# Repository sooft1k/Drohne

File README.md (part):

# Drohne – Flugsteuerung STM32F405

Eigene Flugsteuerung für einen Quadrocopter mit STM32F405RGT6 (STM32-HAL).

Dieser Branch gilt für die neue Platine. Die Firmware ist bisher nur kompiliert
und noch nicht auf der Platine getestet.

| Teil | Anschluss |
|---|---|
| Gyro/Accel | ICM-42688-P an SPI1 (PA4 CS, PA5 SCK, PA6 MISO, PA7 MOSI), 10,5 MHz |
| Barometer | BMP388 an I2C1 (PB6 SCL, PB7 SDA), Adresse 0x76, 400 kHz |
| Kompass | QMC5883L an I2C1, Adresse 0x0D |
| Abstand (ToF) | 5× VL53L1X an I2C3 (PA8 SCL, PC9 SDA), Adressen 0x30–0x34, 400 kHz; je eigenes XSHUT und Interrupt |
| GPS | ATGM336H-6N-74 an USART3 (PB10 TX, PB11 RX), 115200 Baud, NMEA |
| Motoren | TIM3, Oneshot125: M1 = PB0, M2 = PB1, M3 = PC6, M4 = PC7; 143,5–229 µs (BLHeli_S ab Werk), Stopp 125 µs |
| Funk | ELRS-Empfänger, CRSF 420000 Baud an USART1 (PA9 TX, PA10 RX) |
| Kanäle | 1 Roll, 2 Pitch, 3 Gas, 4 Yaw, 7 Modus Angle/Rate, **8 Arm-Schalter (AUX4)** |
| Terminal | USART2 (PA2 TX, PA3 RX), 115200 Baud, über einen USB-Seriell-Adapter |
| Akkuspannung | PC0 (ADC1 Kanal 10), Teiler 11:1 |
| Strom | PC1 (ADC2 Kanal 11), Stromausgang „C“ des ESC – höchstens 3,3 V! |
| Status-LED | PC13, aktiv-low (Low = an) |

Regeltakt 1 kHz über TIM2. Flugmodi Angle (selbstaufrichtend) und Rate (Acro).

> **Arm-Schalter auf Kanal 8 (AUX4)**, Modus-Schalter auf Kanal 7. Mit Funk
> zeigt `rc` beide Kanäle; Kanal 8 muss beim Umlegen zwischen etwa 1000 und
> 2000 wechseln. Vor dem ersten Flug Schritt 20 des Kipptests prüfen.
> Kanal 5 (AUX1) wäre bei ELRS etwas schneller, lässt sich an der
> RadioMaster T8L aber keinem Schalter zuordnen – siehe „Arm-Schalter und
> ELRS“ unter „Failsafe“. Kanal in `RC_CH_ARM` (`Sensors/rc.h`).

## Verdrahtung (eigene Platine)

Dieser Abschnitt beschreibt den Zielzustand. Im Schaltplan fehlen Stand
06.11.2026 noch ESC, ELRS, Terminal, Status-LED und die Messung an PC0 und PC1.
Die Namen Ro, Ru, Cb, Rs und Cs gelten nur in dieser README, im Schaltplan haben
die Bauteile andere Nummern.

Alle Massen (GND) sind miteinander verbunden: Akku-Minus über den ESC, die
Flugsteuerung, Empfänger und der USB-Seriell-Adapter. **Beim Löten
und Anstecken immer zuerst GND verbinden**, dann die Signale.

### Übersicht

| Von | An STM32 | Hinweis |
|---|---|---|
| ESC M1 / M2 / M3 / M4 | PB0 / PB1 / PC6 / PC7 | je 10 kΩ nach GND empfohlen (siehe unten) |
| ESC GND | GND | gemeinsame Masse, Pflicht |
| ESC Strom „C“/„CUR“ | PC1 über 4,7 kΩ, 100 nF nach GND | höchstens 3,3 V am Pin |
| Akku+ (z. B. ESC-Pin „V“/„VBAT“) | PC0 über Teiler 10 kΩ / 1 kΩ, 100 nF | Teiler 11:1 |
| ELRS TX | PA10 (USART1 RX) | |
| ELRS RX | PA9 (USART1 TX) | für die Akku-Telemetrie |
| ELRS 5V / GND | 5 V / GND | |
| ICM-42688-P CS / SCK / MISO / MOSI | PA4 / PA5 / PA6 / PA7 (SPI1) | auf der Platine |
| BMP388 und QMC5883L SCL / SDA | PB6 / PB7 (I2C1) | auf der Platine |
| VL53L1X SCL / SDA | PA8 / PC9 (I2C3) | auf der Platine, Pullups 4,7 kΩ (R16, R17) |
| VL53L1X XSHUT 1–5 | PC8, PB12, PB13, PB14, PB15 | je 10 kΩ nach 3,3 V |
| VL53L1X GPIO1 (INT) 1–5 | PC2, PB4, PB5, PB8, PB9 | je 10 kΩ nach 3,3 V |
| GPS TXD / RXD | PB11 / PB10 (USART3) | auf der Platine |
| USB-Seriell RX / TX | PA2 / PA3 (USART2) | 3,3-V-Pegel, 115200 Baud |
| Status-LED | PC13 über LED und 1 kΩ an +3,3 V | aktiv-low |

### 1. Akkuspannung an PC0

```
 Akku+ (VBAT, bis 25,2 V)
        │
       ┌┴┐
       │ │ Ro  10 kΩ, 1 %, 0,25 W
       └┬┘
        │
        ├──────────┬──────────── PC0  (ADC1, Kanal 10)
        │          │
       ┌┴┐       ──┴──
       │ │ Ru    ─────  Cb  100 nF, Keramik X7R
       └┬┘ 1 kΩ    │
        │   1 %    │
 GND ───┴──────────┴──────────── GND STM32 (= Akku-Minus über den ESC)
```

- **Ro = 10 kΩ, Ru = 1 kΩ**, Metallschicht, 1 %. Teilerfaktor 11:
  25,2 V (6S voll) → 2,29 V an PC0.
- Leistung bei 25,2 V: 25,2² / 11 kΩ ≈ 58 mW im ganzen Teiler, davon rund 52 mW
  in Ro – 0,25-W-Widerstand reicht.
- **Cb = 100 nF** direkt an PC0 nach GND, glättet Störungen der Motoren.
- Ru und Cb möglichst nah am STM32-Pin löten, die lange Leitung kommt an Ro.
- Andere Widerstände gehen auch, dann aber `BAT_R_OBEN` und `BAT_R_UNTEN` in
  `Sensors/battery.h` anpassen. PC0 darf nie mehr als 3,3 V sehen.
- Nach dem ersten Anstecken mit einem Multimeter die Akkuspannung messen
  und `batcal <volt>` eingeben.

### 2. Stromeingang PC1 schützen

```
 ESC "C" / "CUR"
        │
       ┌┴┐
       │ │ Rs  4,7 kΩ
       └┬┘
        │
        ├──────────────────────── PC1  (ADC2, Kanal 11)
        │
      ──┴──
      ─────  Cs  100 nF, Keramik X7R
        │
 GND ───┴──────────────────────── GND STM32
```

- **Rs = 4,7 kΩ in Reihe, Cs = 100 nF von PC1 nach GND**, beide direkt am Pin.
  Zusammen ein Tiefpass mit etwa 340 Hz: Er glättet die PWM-Welligkeit des
  ESC (24/48 kHz), und Rs begrenzt den Strom, falls der Ausgang doch über
  3,3 V geht.
- PC1 verträgt als Analogeingang **höchstens 3,3 V**. Deshalb vorher messen (siehe Punkt 3). Kann
  der Ausgang über 3,0 V gehen, statt Rs allein einen Teiler einbauen:

```
 ESC "C" ──[ 10 kΩ ]──┬── PC1
                      ├──[ 20 kΩ ]── GND
                      └──|| 100 nF ── GND
```

  Der Teiler macht aus 4,5 V dann 3,0 V. Danach `CURR_MV_PER_A_DEFAULT` in
  `battery.h` mit 2/3 multiplizieren (bzw. einfach mit `curcal`
  kalibrieren).

### 3. Woher das Stromsignal kommt

Der B-Cube-4in1 hat einen Stromsensor (Shunt mit Verstärker) für alle vier
Motoren zusammen. Sein Ausgang liegt am 8-poligen Stecker zur Flugsteuerung,
beschriftet mit **„C“, „CUR“ oder „CURR“**. Die Pin-Reihenfolge ist je nach
Version verschieden. Aus der früheren Platinenplanung war sie
`1 GND · 2 VBAT · 3 M1 · 4 M2 · 5 M3 · 6 M4 · 7 C · 8 frei` – **trotzdem am
Aufdruck neben dem Stecker prüfen**, nicht dem Kabel vertrauen.

Mit dem Multimeter (Akku dran, Propeller ab, Motoren aus):

1. **GND:** Durchgang zum Akku-Minus.
2. **VBAT:** zeigt die Akkuspannung.
3. **C/CUR:** zeigt 0 V bis einige 10 mV. Nach dem Armen (Motoren im
   Leerlauf) steigt der Wert leicht. Bei 12,75 mV/A macht 1 A nur 13 mV
   aus.
4. **Höchstwert:** Die Skalierung ist nicht bekannt (12–40 mV/A üblich). Bei
   40 mV/A wären 3,3 V schon bei 82 A erreicht – das kann ein 5-Zoll-Quad
   bei Vollgas erreichen. Deshalb prüfen, woher der Verstärker seine Versorgung
   bekommt: Ist auf der ESC-Platine nur eine 3,3-V-Schiene in der Nähe,
   kann der Ausgang nicht über 3,3 V gehen. Ist es 5 V, den Teiler aus
   Punkt 2 nehmen.

Der Pin „TLM“ (falls vorhanden) bleibt frei – BLHeli_S sendet keine
Telemetrie.

### 4. Motorsignale

```
 PB0 ──┬──── ESC M1        (ebenso PB1→M2, PC6→M3, PC7→M4)
       │
      ┌┴┐
      │ │ 10 kΩ nach GND (empfohlen)
      └┬┘
 GND ──┴──── ESC GND
```

Nach einem Reset sind die STM32-Pins einige Millisekunden lang offen. Liegt
eine Signalleitung dabei auf High, während der ESC startet, kann BLHeli_S in
seinen Bootloader springen und erst wieder reagieren, wenn das Signal läuft. Ein 10-kΩ-Widerstand nach GND an jeder Leitung hält
sie in dieser Zeit sicher auf Low.

### Bauteilliste

| Bauteil | Wert | Anzahl | Wofür |
|---|---|---|---|
| Widerstand 1 %, 0,25 W | 10 kΩ | 1 | Ro Akkuteiler |
| Widerstand 1 % | 1 kΩ | 1 | Ru Akkuteiler |
| Widerstand | 4,7 kΩ | 1 | Rs Strom |
| Widerstand | 10 kΩ | 4 | Pull-down Motorsignale |
| Keramikkondensator X7R | 100 nF | 2 | Cb an PC0, Cs an PC1 |
| optional Widerstand | 10 kΩ + 20 kΩ | je 1 | Teiler am Strom, falls > 3,0 V |

## ESC und Motorsignal (BLHeli_S)

**Der ESC muss nicht umprogrammiert werden.** Die Firmware gibt genau den
Gasbereich aus, den BLHeli_S ab Werk erwartet: PPM Min/Max Throttle
1148/1832 µs, bei Oneshot125 geteilt durch 8.

| Zustand | Pulsbreite | Konstante (`Sensors/motor.h`) |
|---|---|---|
| Disarmed, Start, Notaus | 125 µs – sicher unter dem Minimum, der ESC steht und armt | `MOTOR_US_STOP` |
| Gearmt, 0 % Ausgang | 143,5 µs = ESC-Minimum, Motor steht gerade noch | `MOTOR_US_MIN` |
| Gearmt, Leerlauf | 147,8 µs = 5 % (`MIXER_IDLE_PERCENT`) | |
| Gearmt, 100 % Ausgang | 229 µs = ESC-Maximum | `MOTOR_US_MAX` |

Der Stopp-Puls von 125 µs liegt weit unter dem Maximum – der ESC geht beim
Einschalten nicht in den Programmiermodus (der startet nur, wenn beim
Einschalten Vollgas anliegt).

**Leerlauf prüfen** (Kipptest Schritt 15): Alle vier Motoren müssen im
Leerlauf sicher und gleichmäßig drehen. Stockt einer oder läuft er
unruhig an, `MIXER_IDLE_PERCENT` in `Sensors/mixer.h` in Schritten von 1 %
erhöhen; drehen sie unnötig schnell, senken (nicht unter 2 %).

**Drehrichtung** ohne Linker: Dreht ein Motor falsch herum, zwei seiner drei
Motordrähte tauschen.

### Optional: ESC umprogrammieren

Wer später einen BLHeli-Linker hat (fertiger USB-Linker, Arduino mit der
4-Way-Interface-Firmware aus BLHeliSuite oder vorübergehend eine
Betaflight-Flugsteuerung mit [esc-configurator.com](https://esc-configurator.com)),
kann den Gasbereich etwas weiter stellen und „Programming by TX“
abschalten. Die eigene Flugsteuerung kann kein BLHeli-Passthrough.

| Einstellung | Wert | dann in `motor.h` |
|---|---|---|
| PPM Min Throttle | 1040 µs | `MOTOR_US_MIN 130.0f` |
| PPM Max Throttle | 2000 µs | `MOTOR_US_MAX 250.0f` |
| Programming by TX | aus | – |

**Wichtig:** ESC und `motor.h` müssen immer zusammenpassen. Nur den ESC
umstellen und die Firmware nicht (oder umgekehrt) verschiebt Leerlauf und
Vollgas – im schlimmsten Fall steht ein Motor im Leerlauf oder die oberen
Prozent wirken nicht mehr. `MOTOR_US_STOP` muss immer deutlich unter
`MOTOR_US_MIN` bleiben. Danach den Leerlauf wie oben prüfen.

## Bauen und Flashen

```sh
git submodule update --init --recursive   # STM32CubeF4 mit HAL und CMSIS
make
make flash                                # OpenOCD-Pfad steht im Makefile
```

## Vorzeichenkonvention

Gilt für die ganze Firmware: Lagewinkel, Gyro-Drehraten, Sollwerte und
Reglerausgaben. Die Beschreibung steht auch oben in `Sensors/mixer.c`.

Körperachsen wie in der Luftfahrt, rechtshändig:

- **X** nach vorne, **Y** nach rechts, **Z** nach unten

Positive Drehrichtungen:

| Achse | positiv heißt | Knüppel |
|---|---|---|
| Roll | rechte Seite geht nach unten | Roll rechts → + |
| Pitch | Nase geht nach oben | Pitch nach vorne → − (Nase runter) |
| Yaw | Nase dreht nach rechts (von oben im Uhrzeigersinn) | Yaw rechts → + |

Ein positiver Reglerausgang erzeugt eine Drehung in positiver Richtung.
Der Mixer setzt das so um:

| Stellgröße | mehr Gas | weniger Gas |
|---|---|---|
| Roll + | M3, M4 (links) | M1, M2 (rechts) |
| Pitch + | M2, M4 (vorne) | M1, M3 (hinten) |
| Yaw + | M2, M3 (CCW) | M1, M4 (CW) |

Motorbelegung, Blick von oben:

```
    M4 (CW)    M2 (CCW)     vorne
          \    /
           \  /
           /  \
          /    \
    M3 (CCW)   M1 (CW)      hinten
```

### Einbaulage des Sensors

Der ICM-42688-P liegt mit der Bauteilseite nach oben. In `Sensors/icm42688.h`
wird eingestellt, wohin die X-Achse des Chips zeigt. Das hängt vom Layout ab:

```c
#define IMU_ALIGN IMU_X_VORNE   /* oder IMU_X_RECHTS, IMU_X_HINTEN, IMU_X_LINKS */
```

Die Firmware rechnet die Chip-Achsen damit auf die Körperachsen um.

## Kipptest ohne Propeller

Vor jedem Erstflug und nach jeder Änderung an Sensor, Mixer oder Verkabelung.
**Propeller ab.**

### Teil A – Sensor (kein Akku)

1. Flugsteuerung flach hinlegen, Nase nach vorne. Strom kommt über die
   USB-Buchse der Platine. Die Firmware hat dort kein Terminal, deshalb einen
   USB-Seriell-Adapter an USART2 (PA2/PA3) mit 115200 Baud anschließen. Reset
   drücken und bis `>> Bereit.` nicht bewegen
   (Gyro-Kalibrierung). Wird sie bewegt, meldet die Firmware „Bewegung
   erkannt“ und misst neu (bis zu 5 Versuche). Klappt keiner, bleibt Arming
   bis zum Neustart gesperrt. Die Lagewinkel starten direkt mit dem Wert aus
   dem Beschleunigungssensor.
2. `stream on` eingeben. Flach liegend: `R` und `P` nahe 0, `Gx`, `Gy`, `Gz`
   nahe 0.
3. Rechte Seite etwa 30° nach unten kippen: `R` wird positiv (ungefähr +30).
4. Nase etwa 30° nach oben kippen: `P` wird positiv.
5. Flach liegend von oben gesehen im Uhrzeigersinn drehen (Nase nach rechts):
   `Gz` ist während der Drehung positiv.
6. Stimmt Schritt 3 oder 4 nicht, ist die Einbaulage falsch eingestellt.
   Beobachtung bei der Einstellung `IMU_X_VORNE`:

   | Rechte Seite runter | Nase hoch | richtige Einstellung |
   |---|---|---|
   | R + | P + | `IMU_X_VORNE` (passt) |
   | R − | P − | `IMU_X_HINTEN` |
   | P − | R + | `IMU_X_RECHTS` |
   | P + | R − | `IMU_X_LINKS` |

   Zeigt `R` flach liegend etwa ±180, liegt der Chip kopfüber. Das wird nicht
   unterstützt, Sensor mit der Bauteilseite nach oben einbauen.
7. `stream off`.

### Teil B – Regler und Mixer (kein Akku, disarmed)

8. `angle` eingeben (bei verbundener Funke: Modus-Schalter auf Angle),
   dann `kipp`. Das zeigt fünfmal pro Sekunde, was der Mixer bei 50 % Gas
   ausgeben würde. Die Motoren bleiben aus. Flach liegend stehen alle vier
   Werte etwa gleich (52,5).
9. Nase etwa 20° nach unten drücken: **M2 und M4 (vorne) höher** als M1 und
   M3. Der Regler will die Nase wieder anheben.
10. Rechte Seite etwa 20° nach unten: **M1 und M2 (rechts) höher** als M3 und M4.
11. Flach liegend im Uhrzeigersinn drehen: während der Drehung **M1 und M4
    (CW) höher** als M2 und M3. Der Regler bremst die Drehung.
12. Mit verbundener Funke (Arm-Schalter unten), flach liegend:
    - Roll-Knüppel rechts → **M3 und M4 höher** (linke Seite hebt sich)
    - Pitch-Knüppel nach vorne → **M1 und M3 höher** (Heck hebt sich)
    - Yaw-Knüppel rechts → **M2 und M3 höher**
13. `kipp` beendet die Anzeige.

Ist in Teil B eine Richtung verkehrt, obwohl Teil A stimmt: nicht fliegen.
Die Vorzeichen in `mixer.c` nicht einfach umdrehen – sie folgen der
Konvention oben. Der Fehler liegt dann woanders (Einbaulage, Verkabelung).

### Teil C – Motoren (Akku dran, Propeller ab)

14. Funke an, Arm-Schalter unten, Gas ganz unten. Akku anstecken.
15. Drohne etwa 30° schräg halten und den Arm-Schalter hochnehmen: Die
    Motoren bleiben aus, das Terminal meldet `Arming abgelehnt: zu schief`.
    Arm-Schalter wieder runter, Drohne flach hinstellen.
    Arm-Schalter hoch: Alle vier Motoren laufen im Leerlauf. Drehrichtung
    jedes Motors prüfen (Klebeband-Fähnchen auf der Glocke), von oben gesehen:
    M1 hinten rechts CW, M2 vorne rechts CCW, M3 hinten links CCW,
    M4 vorne links CW. Dreht ein Motor falsch herum: zwei der drei
    Motordrähte tauschen oder, mit einem BLHeli-Linker, im ESC-Configurator
    („Motor Direction“) umstellen – nie die Vorzeichen im Mixer ändern.
16. Modus Angle, Gas auf etwa 30 %, Drohne gut festhalten:
    - Nase nach unten kippen → die vorderen Motoren laufen schneller.
    - Rechte Seite nach unten → die rechten Motoren laufen schneller.
17. Drohne flach halten, Gas ganz zurück: Die Motoren laufen im Leerlauf
    weiter und gehen nicht aus. (Weil das Gas in Schritt 16 schon über 25 %
    war, ist jetzt Airmode aktiv: Schräg gehalten würden die tieferen Motoren
    weiter hochdrehen. Siehe „Leerlauf und Gas“.)
    Terminal-Test: `disarm` eingeben, während der Arm-Schalter noch oben ist.
    Die Motoren gehen aus und bleiben aus, bis der Schalter einmal unten war.
18. Failsafe: Gas auf etwa 30 %, dann die Funke ausschalten. Nach 0,5 s
    nimmt die Firmware das Gas in 1,5 s auf Leerlauf zurück und schaltet
    danach die Motoren ab. Funke wieder an: Die Motoren bleiben aus, bis der
    Arm-Schalter einmal unten war.
19. Arm-Schalter während der Rampe (nur, wenn sich die Verbindung schnell
    unterbrechen und wiederherstellen lässt, z. B. am Sender das interne
    HF-Modul kurz auf AUS und zurück): armen, Gas etwa 30 %, Verbindung
    unterbrechen, nach etwa 1 s wiederherstellen und sofort den Arm-Schalter
    runter: Motoren sofort aus. Vorher zum Armen Gas ganz runter. Ein
    Neustart des Senders dauert zu lang – dann hat die Rampe schon
    abgeschaltet und der Test sagt nichts aus.
20. Gas ganz unten, Arm-Schalter hoch (Motoren im Leerlauf), dann
    Arm-Schalter runter: Motoren sofort aus.

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
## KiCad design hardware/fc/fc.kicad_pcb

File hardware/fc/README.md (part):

# Flight Controller – KiCad-Projekt

Eigene FC-Platine für die 5-Zoll-Drohne nach `fc-spezifikation.md` (Vorgabe des Nutzers, liegt nicht im Repo; die
Spalte „Spezifikation“ der Abweichungstabelle bezieht sich darauf).
Erstellt mit KiCad 7.0 (öffnet auch in KiCad 8/9; dabei wird einmalig konvertiert).

| Datei | Inhalt |
|---|---|
| `fc.kicad_pro` | Projekt mit Designregeln und Netzklassen |
| `fc.kicad_sch` | Schaltplan (ein A1-Blatt, nach Funktionsgruppen, Netzlabels + Versorgungssymbole) |
| `fc.kicad_pcb` | Platine: 42 × 41 mm, 4 Lagen, platziert und vollständig geroutet |
| `fc_custom.kicad_sym` | Projektsymbole: ICM-42688-P, Versorgungssymbole VBAT, +3V3A und +4V5 |
| `fc_custom.pretty` | LMR33630-Footprint ohne Kupfer auf der Unterseite (dort sitzen Steckverbinder); USB-C-Buchse mit an der Platinenkante gekürztem Bestückungsdruck |
| `fertigung/` | Gerber + Bohrdateien (ZIP für JLCPCB), Stückliste und Bestückkoordinaten für beide Seiten, Prüfliste |
| `docs/` | Schaltplan als PDF, Lagenbilder (oben, unten gespiegelt, Lage 2, Lage 3), 3D-Ansichten, DRC- und ERC-Bericht, Routing-Kennzahlen |
| `scripts/` | Generatoren – alles wird aus `scripts/design.py` erzeugt |

## Neu erzeugen

```
export KICAD7_FOOTPRINT_DIR=/usr/share/kicad/footprints
cd hardware/fc
mkdir -p build
python3 scripts/gen_lib.py      # Projektbibliothek
python3 scripts/gen_sch.py      # Schaltplan
kicad-cli sch export netlist -o build/fc.net fc.kicad_sch
python3 scripts/check_netlist.py build/fc.net   # Schaltplan == design.py, Pin für Pin
python3 scripts/gen_pcb.py      # Umriss, Bohrungen, Platzierung, Flächen, Handverdrahtung, Fanout
python3 scripts/route.py        # Autorouting (Freerouting 2.0.1, Java) + Nachrouter, Zonen füllen
python3 scripts/run_drc.py fc.kicad_pcb build/drc.rpt
python3 scripts/report.py fc.kicad_pcb build/fc.net   # Kennzahlen + Abgleich Platine/Schaltplan
python3 scripts/sync_fields.py  # nur Werte/LCSC-Nummern in die geroutete Platine uebernehmen
python3 scripts/fab.py          # Gerber, Bohrdaten, ZIP, JLCPCB-BOM/CPL (beide Seiten), Pruefliste
# Doku (docs/)
cp build/drc.rpt docs/fc_drc_bericht.txt
python3 scripts/report.py fc.kicad_pcb build/fc.net > docs/fc_routing_kennzahlen.txt
python3 scripts/kontur.py > docs/fc_aussenkontur.txt
python3 scripts/render.py fc.kicad_pcb build/fc top,bot,in1,in2 && cp build/fc_{top,bot,in1,in2}.png docs/
kicad-cli sch export pdf -o docs/fc_schaltplan.pdf fc.kicad_sch
```

ERC und 3D-Ansichten mit KiCad 9 (kicad-cli 7 kann beides nicht):
`kicad-cli sch erc --format report --severity-all -o erc.rpt fc.kicad_sch`, für die 3D-Bilder
`kicad-cli pcb render --side top|bottom --quality high --floor -w 1800 -h 1800 -o docs/fc_3d_oben.png fc.kicad_pcb`
(schräg: `--perspective --rotate 305,0,330 --zoom 0.75` bzw. `--side bottom --rotate 55,0,210`).
Die JST-SH-3D-Modelle gibt es dort nur als `.step`; in einer Arbeitskopie der Platine die
`.wrl`-Verweise der Buchsen auf `.step` ändern.

`route.py` probiert für den ersten Freerouting-Lauf bis zu sechs Parametersätze (Via- und
Rip-up-Kosten) und nimmt den ersten vollständigen; bleiben Verbindungen offen, folgen bis zu
drei weitere Freerouting-Läufe auf dem gerouteten Stand und zuletzt ein eigener Nachrouter
(A*-Suche auf 0,1-mm-Raster, F.Cu/B.Cu mit Vias, darf notfalls Autorouter-Bahnen eines anderen
Netzes aufreißen und neu verlegen). Freerouting ist nicht vollständig deterministisch – ein
neuer Lauf ergibt ein anderes, ebenfalls zu prüfendes Routing. Maßgeblich ist die eingecheckte
`fc.kicad_pcb`.

## Lagenaufbau

| Lage | Verwendung |
|---|---|
| 1 F.Cu | Bauteile, Signale, Restfläche GND |
| 2 In1.Cu | durchgehende GND-Fläche (nur Via-Durchbrüche, keine Leiterbahnen, keine Schlitze) |
| 3 In2.Cu | Versorgung: +3V3 (Mitte unter MCU/Gyro/Flash), +5V (Ost, Süd, West), VBAT (Ring am Rand: Nordband zum Regler, schmale Streifen West/Süd zum Verpolschutz). Die 4,5-V-Schiene (+4V5) hat keine Fläche, sie ist als Leiterbahn (0,4 mm, am Diodenknoten 0,6 mm) auf F.Cu/B.Cu verlegt |
| 4 B.Cu | Steckverbinder (JST-SH, außer ELRS/I²C/GPS), Signale, Restfläche GND |

Keine Leiterbahn auf Lage 2 und 3 – dort liegen nur Flächen. Montagebohrungen M3
(Ø 3,2 mm) auf 30,5 × 30,5 mm; nur **H2 (Südost, neben dem ESC-Stecker)** ist mit GND
verbunden, die anderen drei sind nicht durchkontaktiert und haben 3,3 mm Kupfer-Sperrkreis
für die Abstandshalter.

## Flugrichtung

**Vorn ist die Nordkante.** Sie ist auf der Oberseite mit „VORNE“ und zwei Pfeilen markiert.
Von oben gesehen, vorn oben: der ESC-Stecker J2 liegt hinten (Unterseite, Südkante), USB-C
rechts (Ostkante), ELRS/I²C/GPS links (Westkante). Alle Lageangaben in dieser Datei
(Nord/Süd/Ost/West, oben/unten im Bild) beziehen sich auf diese Ansicht.

## Pinbelegung STM32F405RGT6 (für die Firmware)

Die Fallstricke für die Firmware stehen gesammelt im Abschnitt
[Firmware-Hinweise](#firmware-hinweise) (NOVBUSSENS, DMA-Konflikt, Gyro-Ausrichtung).

| Pin | Port | Netz | Funktion |
|---|---|---|---|
| 26 | PB0 | M1 | TIM3_CH3 (wie bisher, `Sensors/motor.c`) – DMA-Konflikt siehe Firmware-Hinweise |
| 27 | PB1 | M2 | TIM3_CH4 (wie bisher) |
| 22 | PA6 | M3 | TIM3_CH1 (wie bisher) |
| 23 | PA7 | M4 | TIM3_CH2 (wie bisher) |
| 8 | PC0 | VBAT_SENSE | ADC123_IN10, Teiler 100 k / 10 k (11:1) |
| 20 | PA4 | CURR_SENSE | **ADC12_IN4** (ADC1 oder ADC2, Kanal 4), Strommessausgang „C“ des ESC (J2 Pin 7) über 1 k / 100 nF – unverändert |
| 55 | PB3 | SPI1_SCK | Gyro + Flash |
| 56 | PB4 | SPI1_MISO | Gyro + Flash |
| 57 | PB5 | SPI1_MOSI | Gyro + Flash |
| 58 | PB6 | GYRO_CS | 10 k Pull-up |
| 52 | PC11 | GYRO_INT1 | EXTI11 (Data-Ready) |
| 59 | PB7 | GYRO_INT2 | Gyro-Pin 9 (INT2/FSYNC/CLKIN), TIM4_CH2 → optional 32-kHz-CLKIN |
| 51 | PC10 | FLASH_CS | 10 k Pull-up |
| 42 | PA9 | ELRS_TX | USART1_TX (wie bisher) – **PA9 ist zugleich VBUS-Erkennung des USB: NOVBUSSENS setzen**, siehe Firmware-Hinweise |
| 43 | PA10 | ELRS_RX | USART1_RX (wie bisher) |
| 16 | PA2 | DBG_TX | USART2_TX (wie bisher) |
| 17 | PA3 | DBG_RX | USART2_RX (wie bisher) |
| 53 | PC12 | GPS_TX | UART5_TX |
| 54 | PD2 | GPS_RX | UART5_RX |
| 37 | PC6 | VTX_TX | USART6_TX |
| 38 | PC7 | VTX_RX | USART6_RX |
| 61 | PB8 | I2C_SCL | I2C1 (AF4) – **neu: bisher PB6** |
| 62 | PB9 | I2C_SDA | I2C1 (AF4) – **neu: bisher PB7** |
| 44 | PA11 | USB_DM | USB OTG FS |
| 45 | PA12 | USB_DP | USB OTG FS |
| 46 | PA13 | SWDIO | |
| 49 | PA14 | SWCLK | |
| 2 | PC13 | LED_ARM | LED rot (Druck „A“), **aktiv-low** (Pin = 0 → LED an) |
| 3 | PC14 | LED_ERR | LED gelb (Druck „E“), aktiv-low |
| 4 | PC15 | LED_LINK | LED grün (Druck „L“), aktiv-low |
| 14 | PA0 | BUZZER | TIM5_CH1 (AF2) bzw. TIM2_CH1 (AF1), high = Piepser an (N-FET AO3400A). TIM2 ist in der Firmware der Regeltakt – für Ton-PWM TIM5 nehmen |
| 9 | PC1 | GPIO1 | Buchse GPIO (J10) Pin 1 |
| 10 | PC2 | GPIO2 | Pin 2 |
| 11 | PC3 | GPIO3 | Pin 3 |
| 25 | PC5 | GPIO4 | Pin 4 |
| 21 | PA5 | GPIO5 | Pin 5 |
| 24 | PC4 | GPIO6 | Pin 6 |
| 5/6 | PH0/PH1 | OSC_IN/OUT | 8-MHz-Quarz (PH1 über 0-Ω-Brücke R3) |
| 60 | BOOT0 | BOOT0 | 10 k nach GND, Lötbrücke JP1 nach 3,3 V = DFU |
| 28 | PB2 | BOOT1 | 10 k nach GND (für zuverlässigen DFU-Start) |
| 7 | NRST | NRST | 100 nF, auch an SWD |

Frei: PA1, PA8, PA15, PB10–PB15, PC8, PC9.

Die Motorpins sind beim Umbau von J2 unverändert geblieben (passend zu `Sensors/motor.c`);
umgebaut ist nur der Stecker. M3/M4 und M1/M2 kreuzen sich deshalb auf dem kurzen Weg zum
ESC-Stecker (je ein Via).

## Firmware-Hinweise

### 1. USB: NOVBUSSENS setzen

PA9 ist USART1_TX (ELRS) und zugleich der VBUS-Erkennungspin des USB-OTG-FS. VBUS ist auf
dieser Platine an **keinen** Prozessorpin geführt. Die VBUS-Erkennung muss deshalb **aus**
sein, sonst wartet der USB-Kern auf VBUS an PA9 (dort liegt das ELRS-Sendesignal) und der FC
meldet sich am PC nicht an.

- Register: `OTG_FS_GCCFG.NOVBUSSENS = 1`, `VBUSASEN = 0`, `VBUSBSEN = 0`
- STM32Cube-HAL: `hpcd_USB_OTG_FS.Init.vbus_sensing_enable = DISABLE;` (setzt genau das).
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
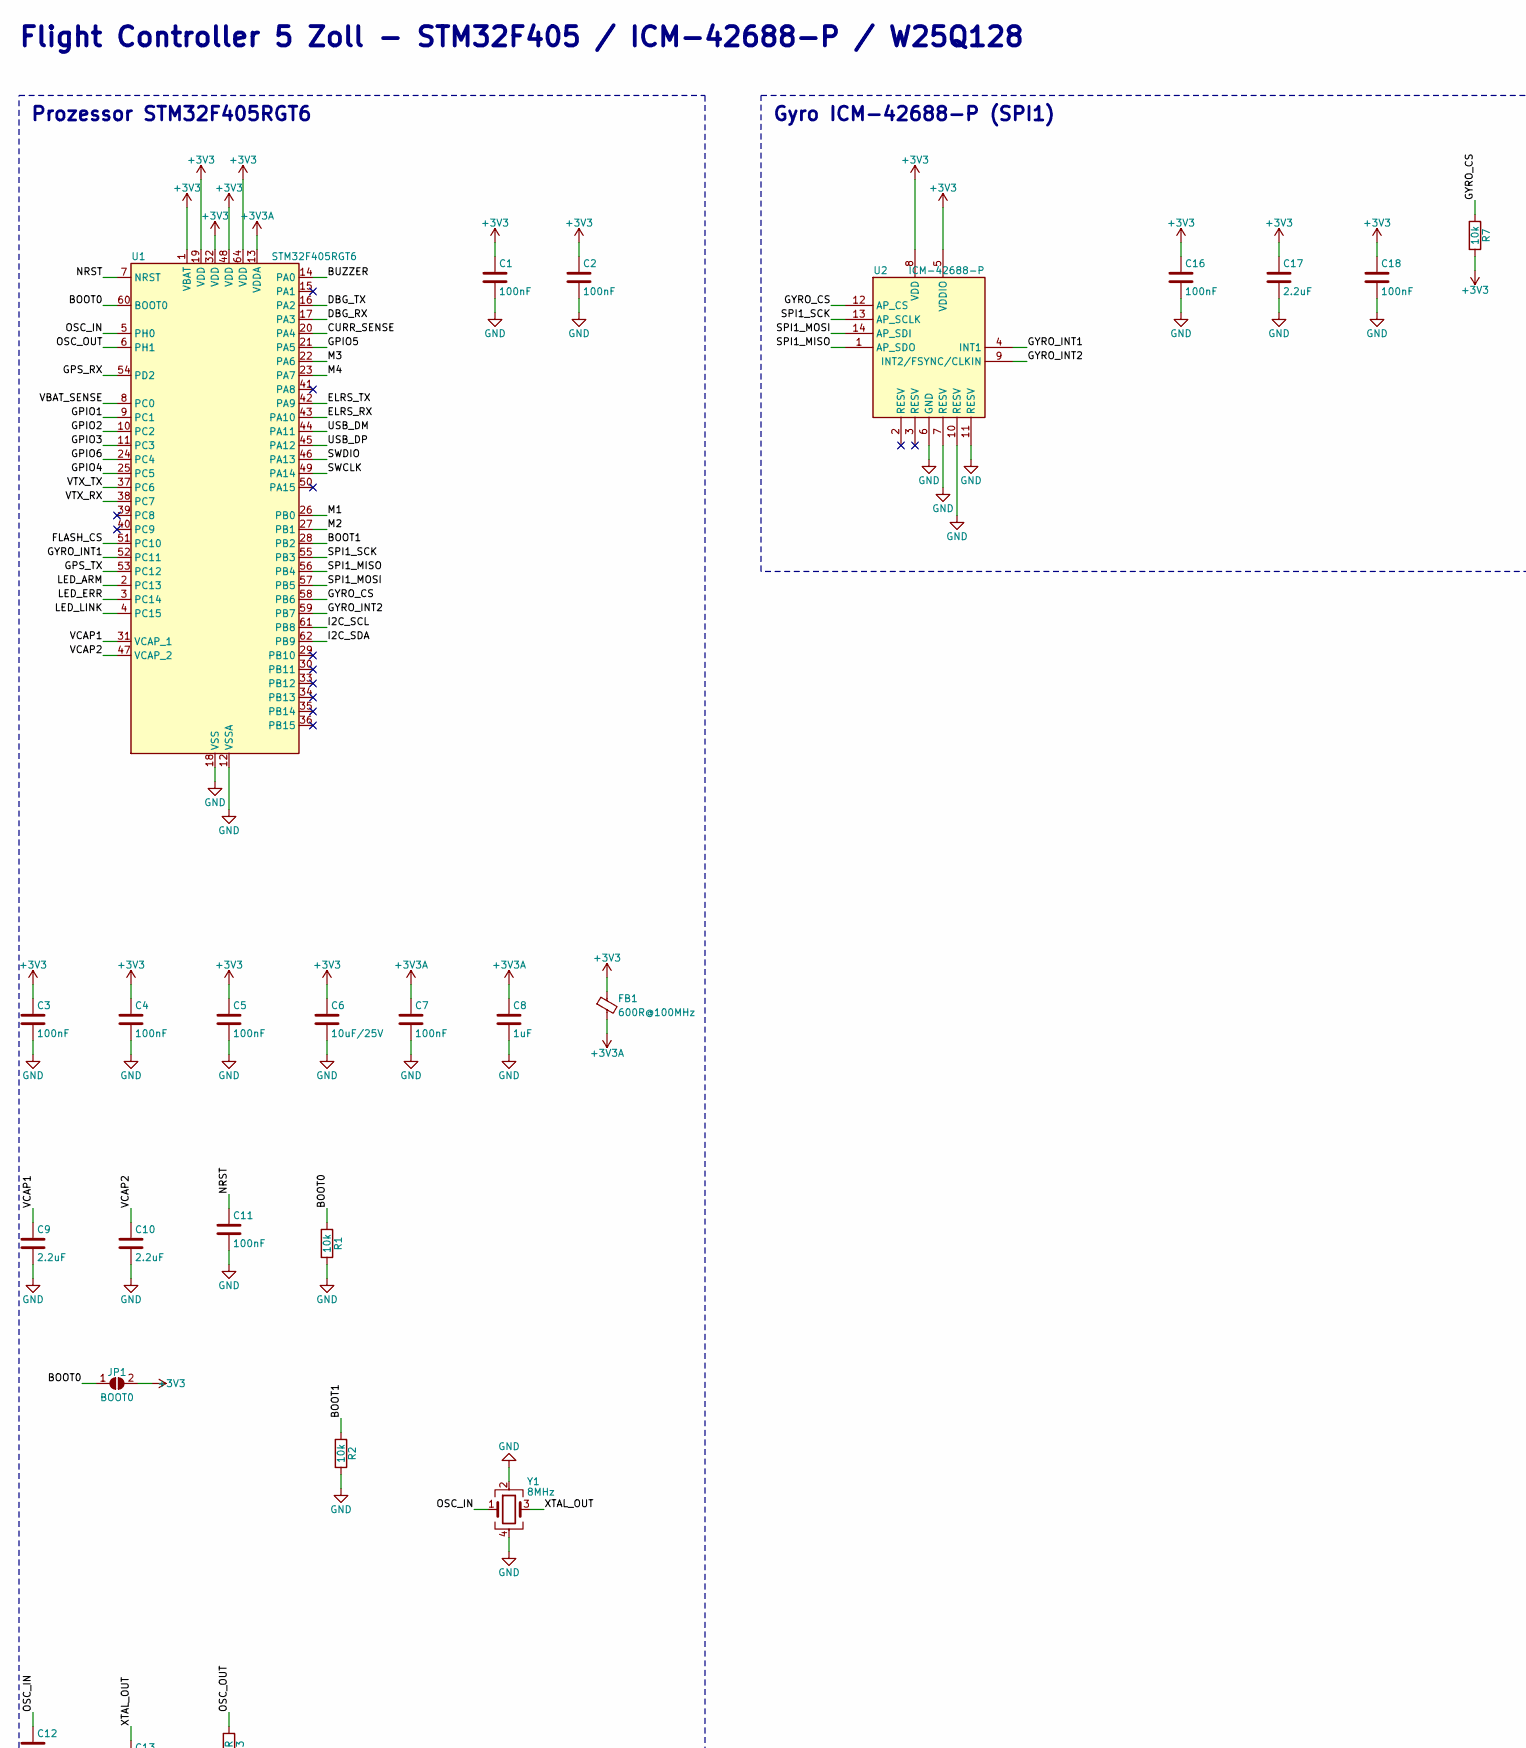
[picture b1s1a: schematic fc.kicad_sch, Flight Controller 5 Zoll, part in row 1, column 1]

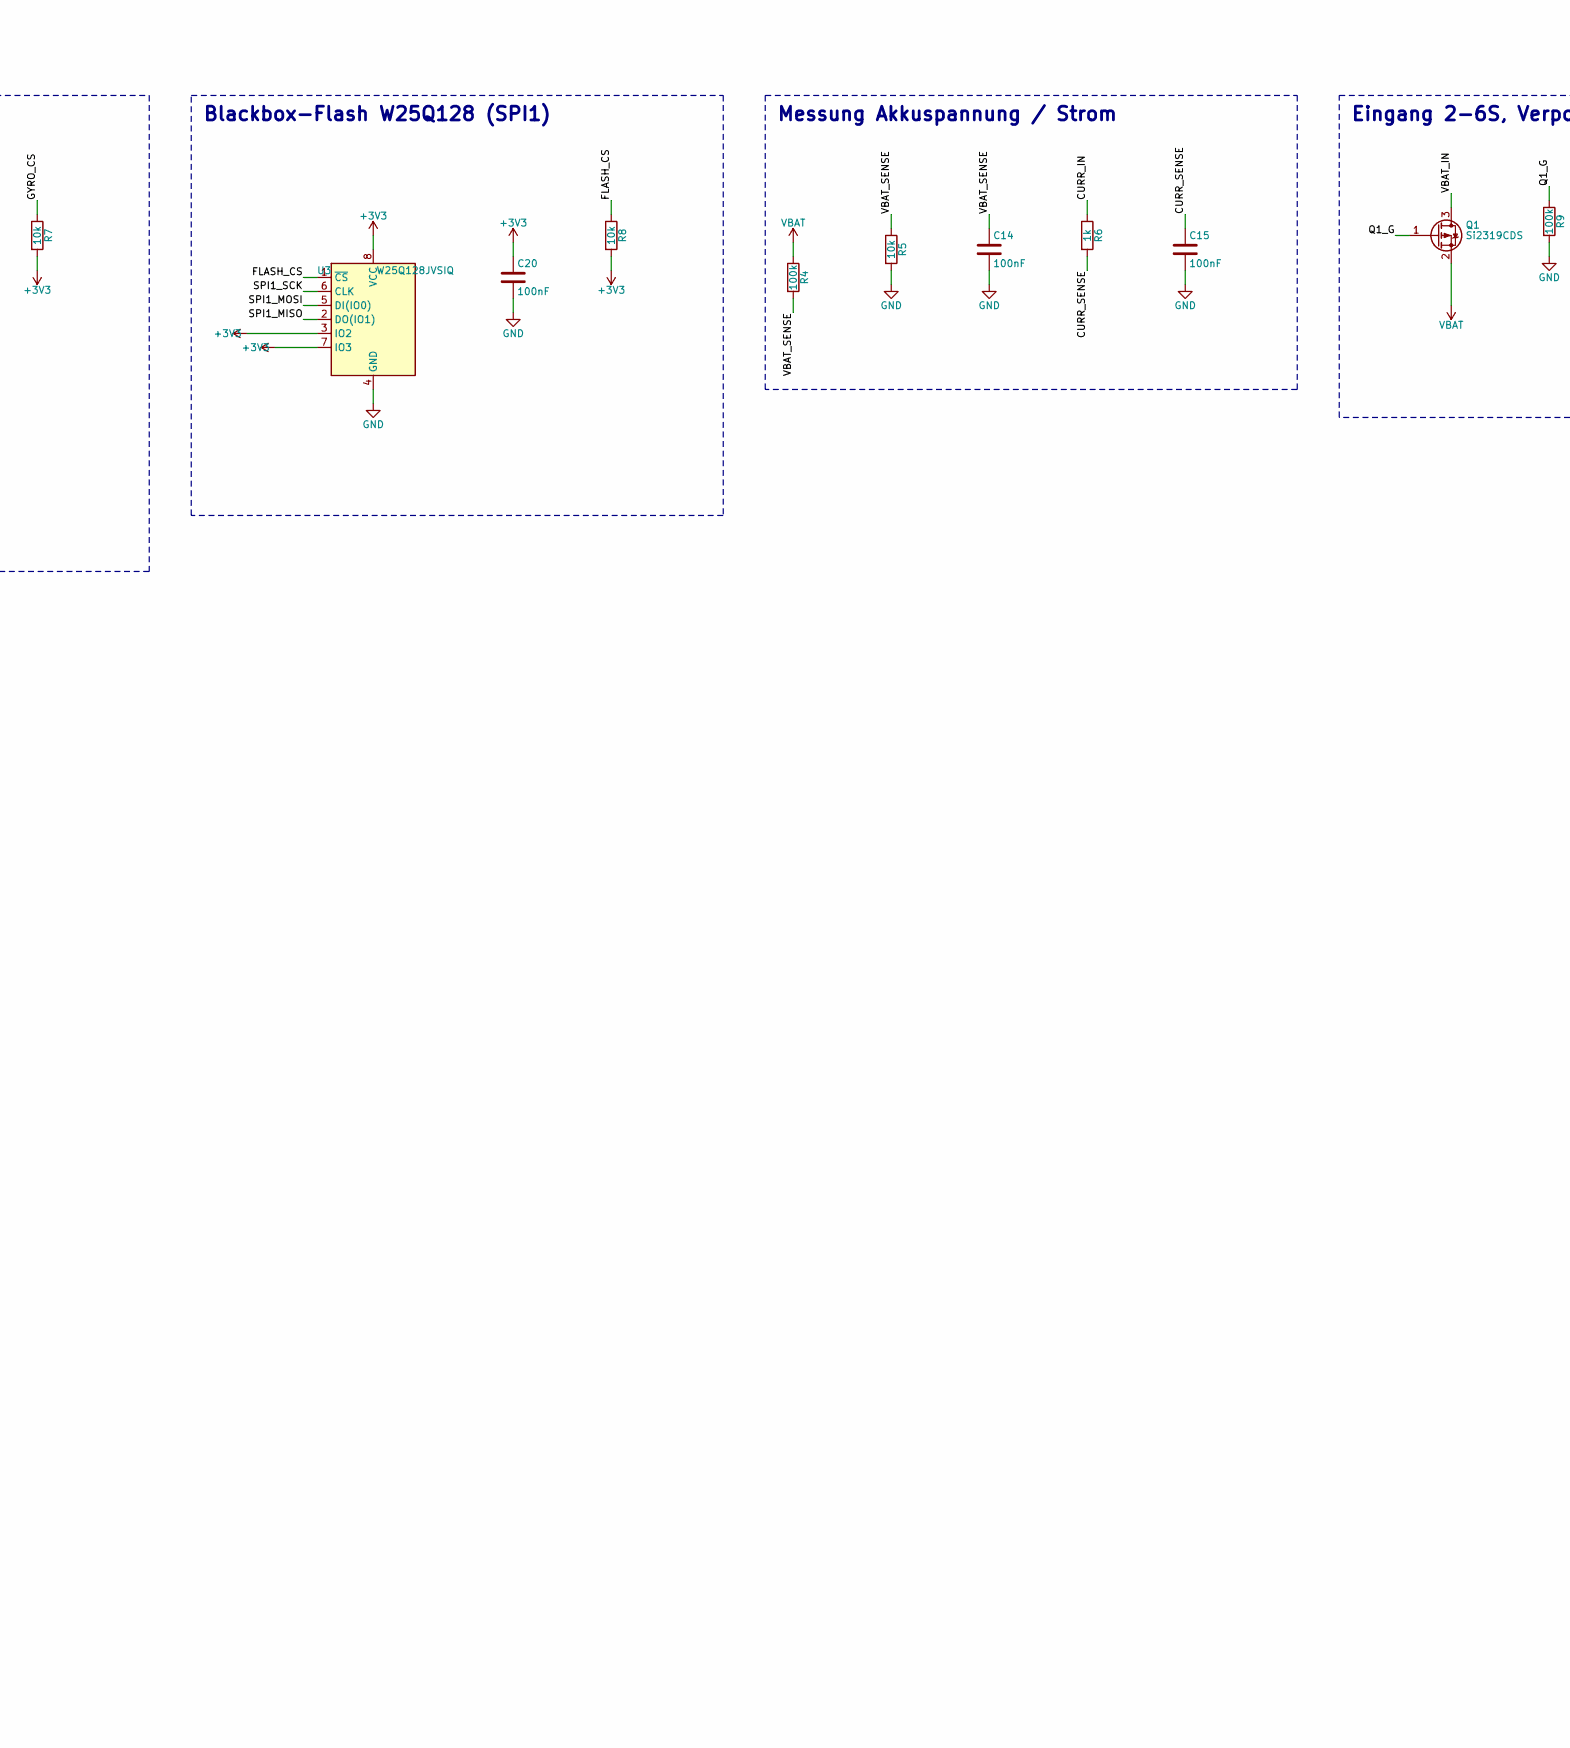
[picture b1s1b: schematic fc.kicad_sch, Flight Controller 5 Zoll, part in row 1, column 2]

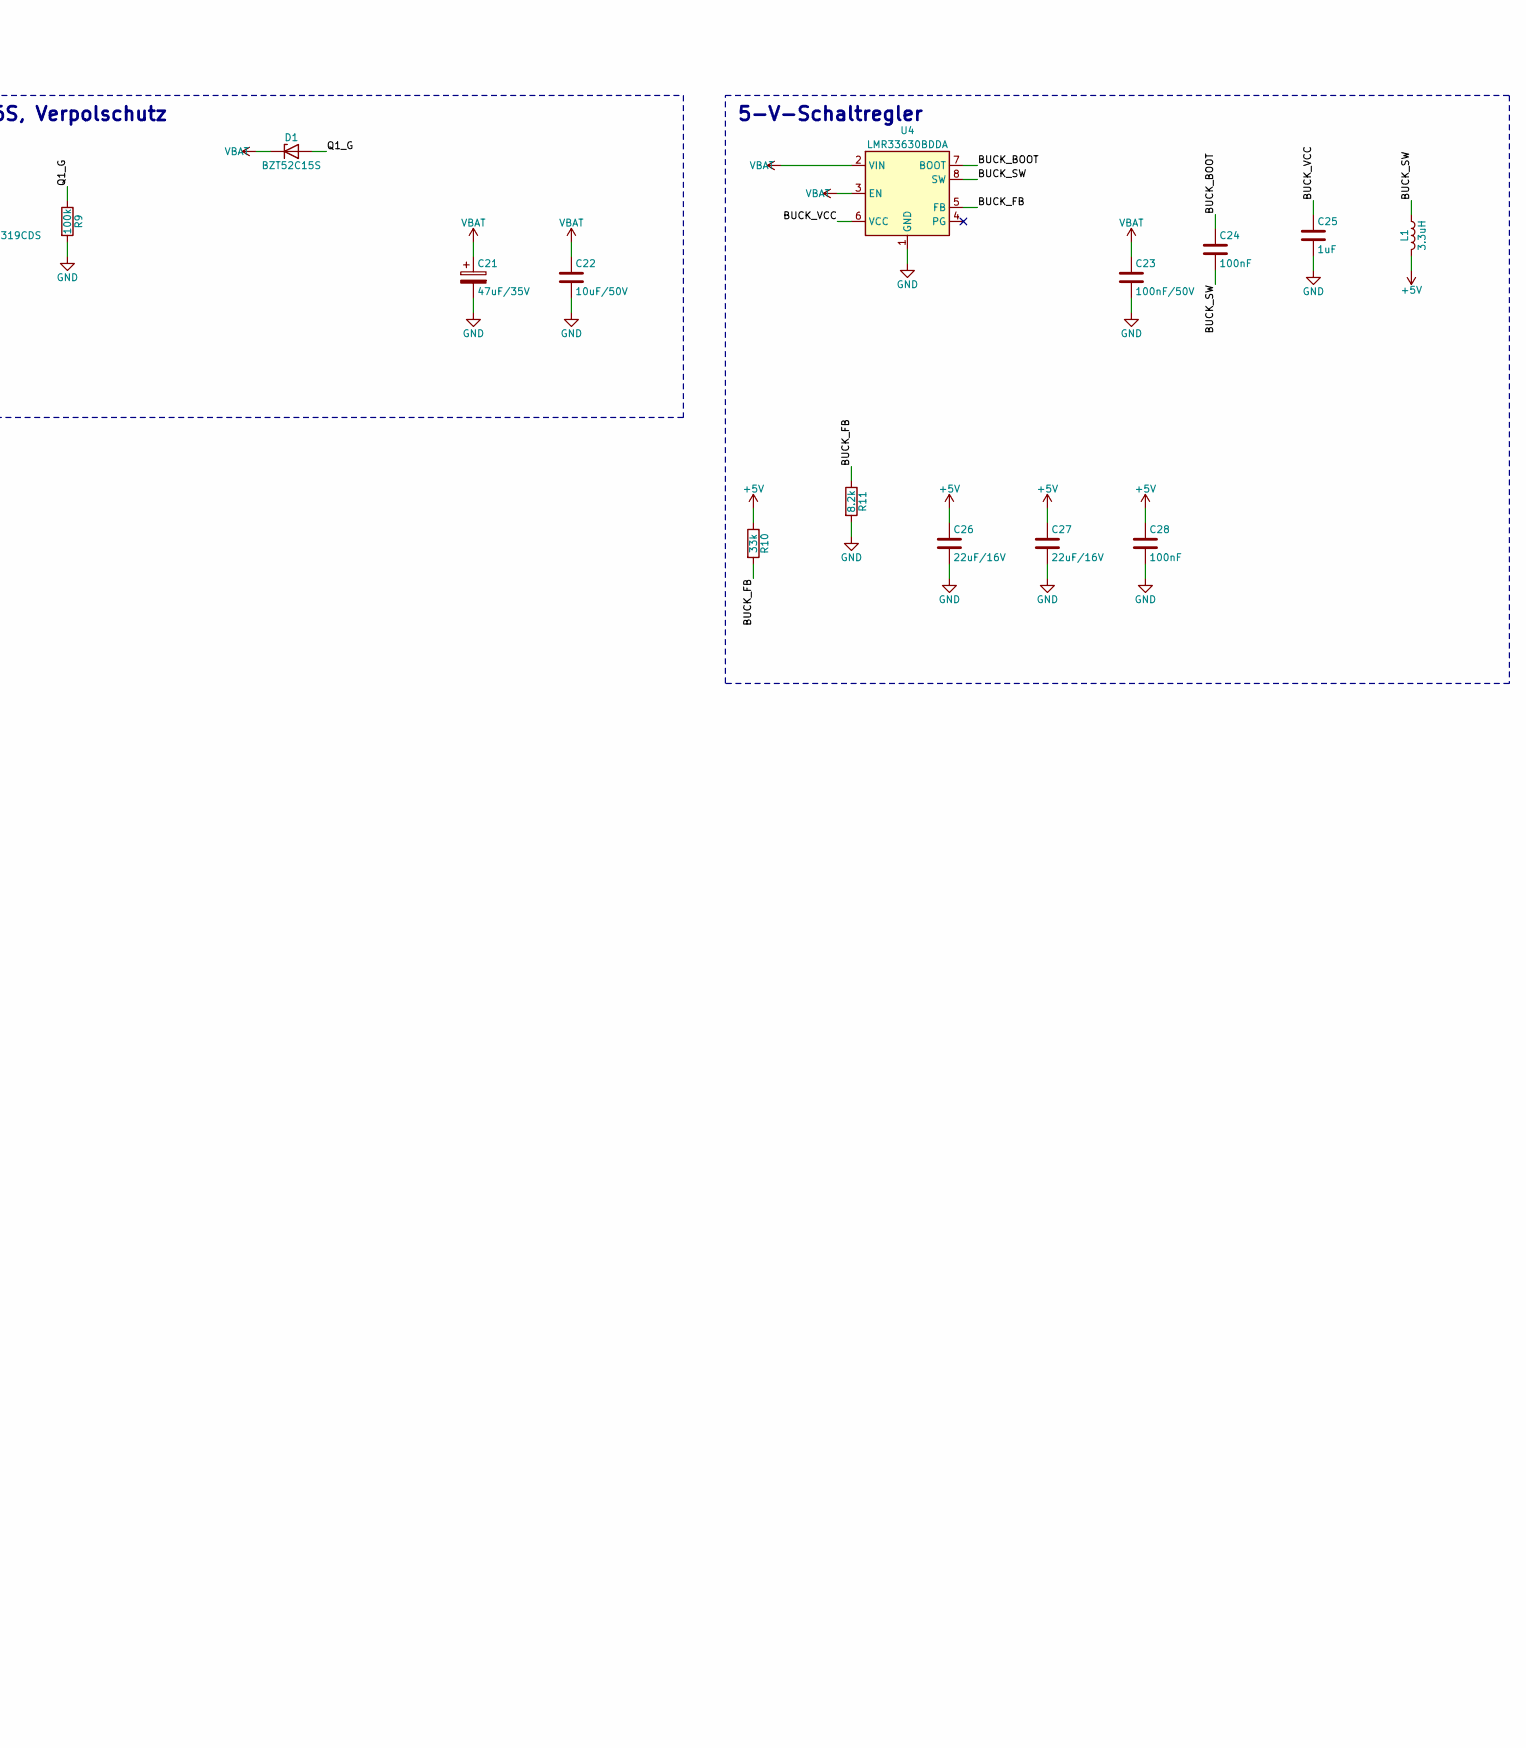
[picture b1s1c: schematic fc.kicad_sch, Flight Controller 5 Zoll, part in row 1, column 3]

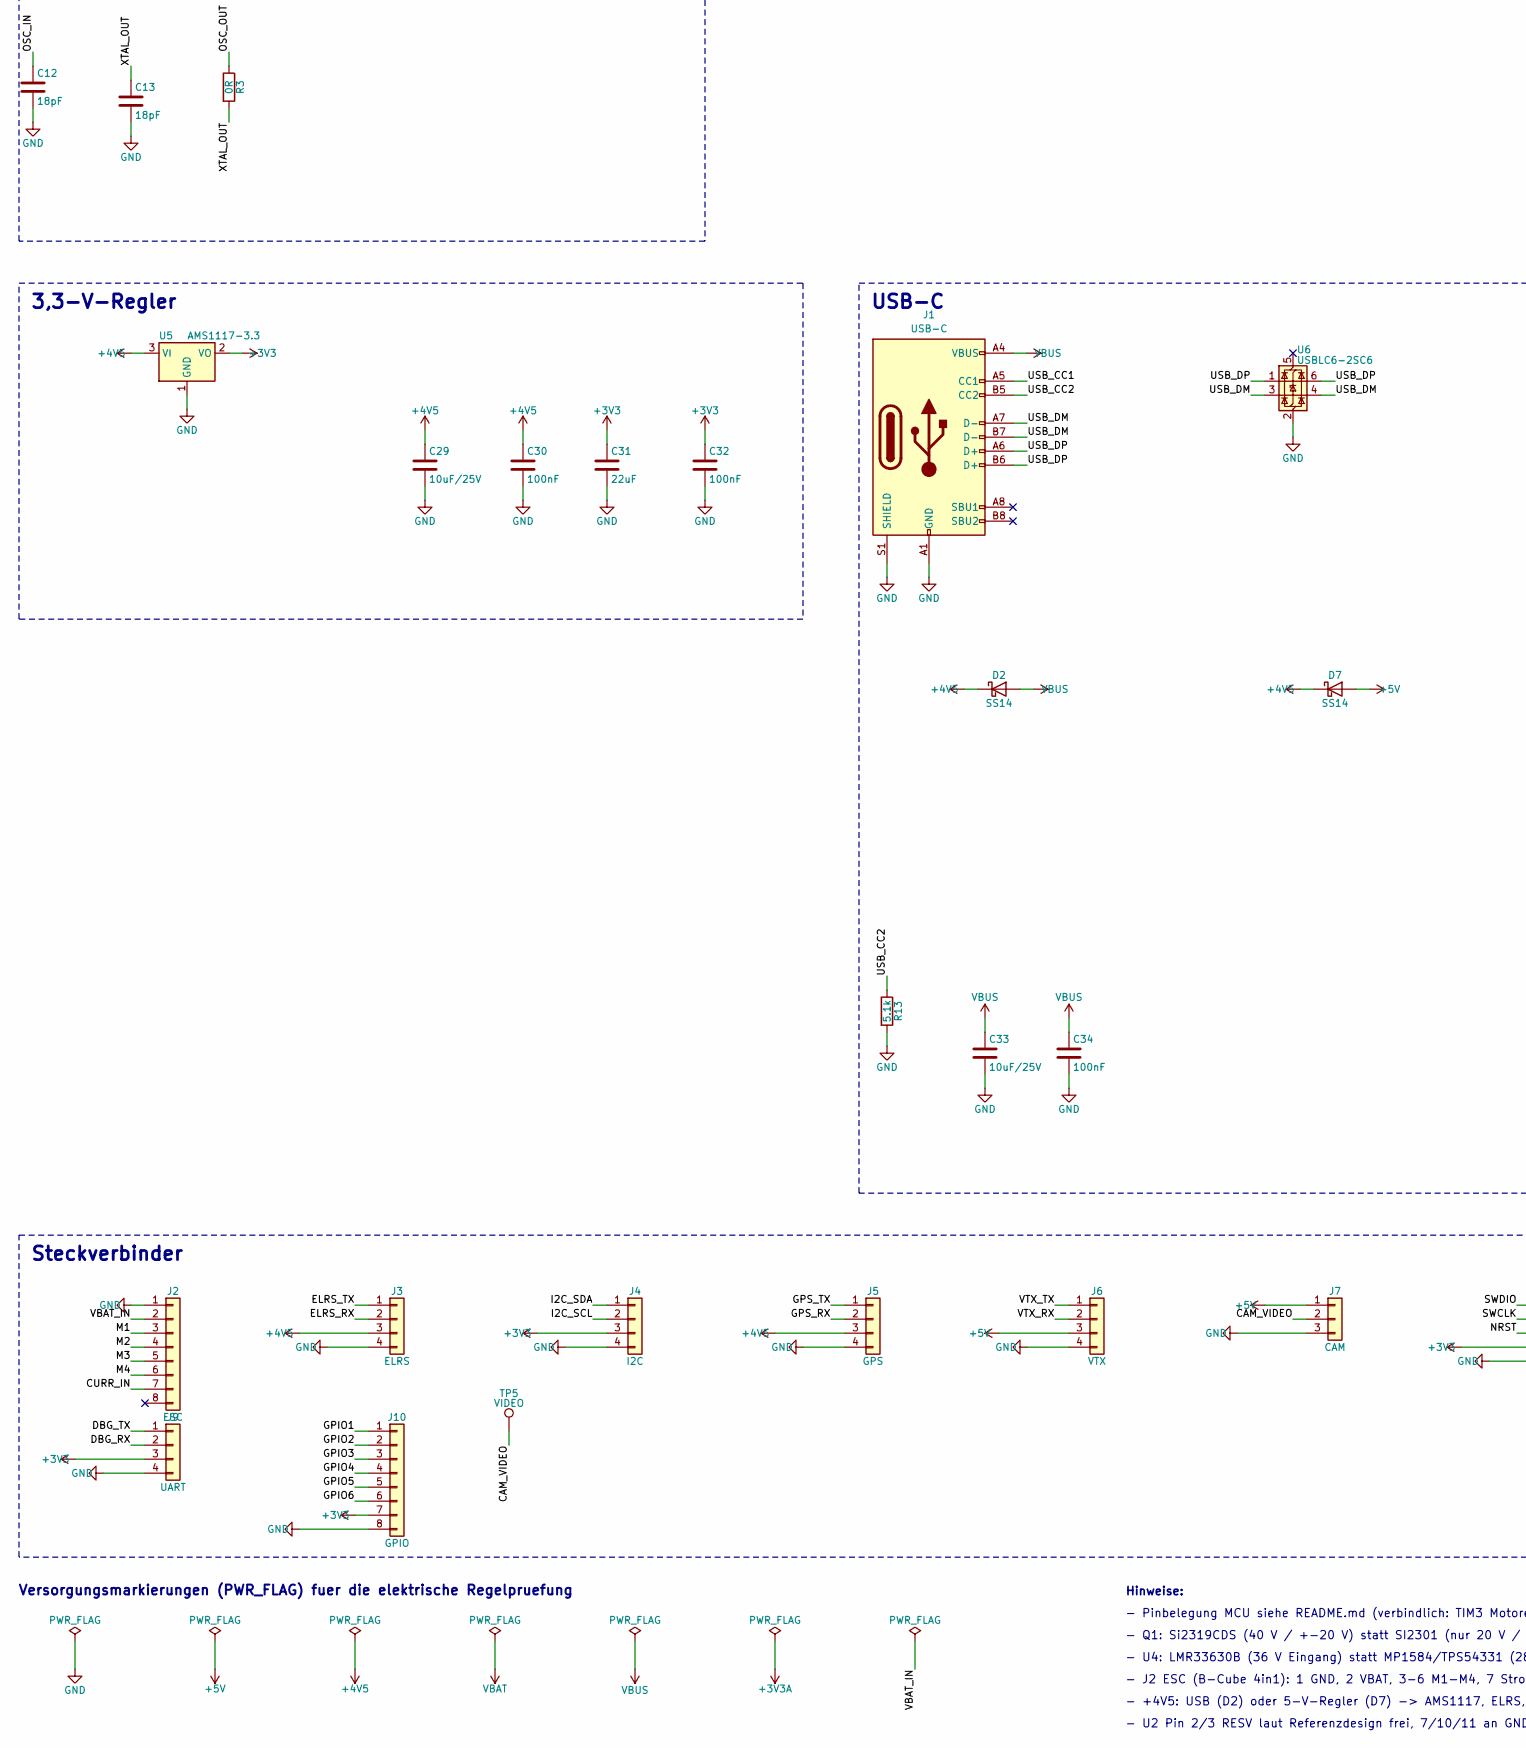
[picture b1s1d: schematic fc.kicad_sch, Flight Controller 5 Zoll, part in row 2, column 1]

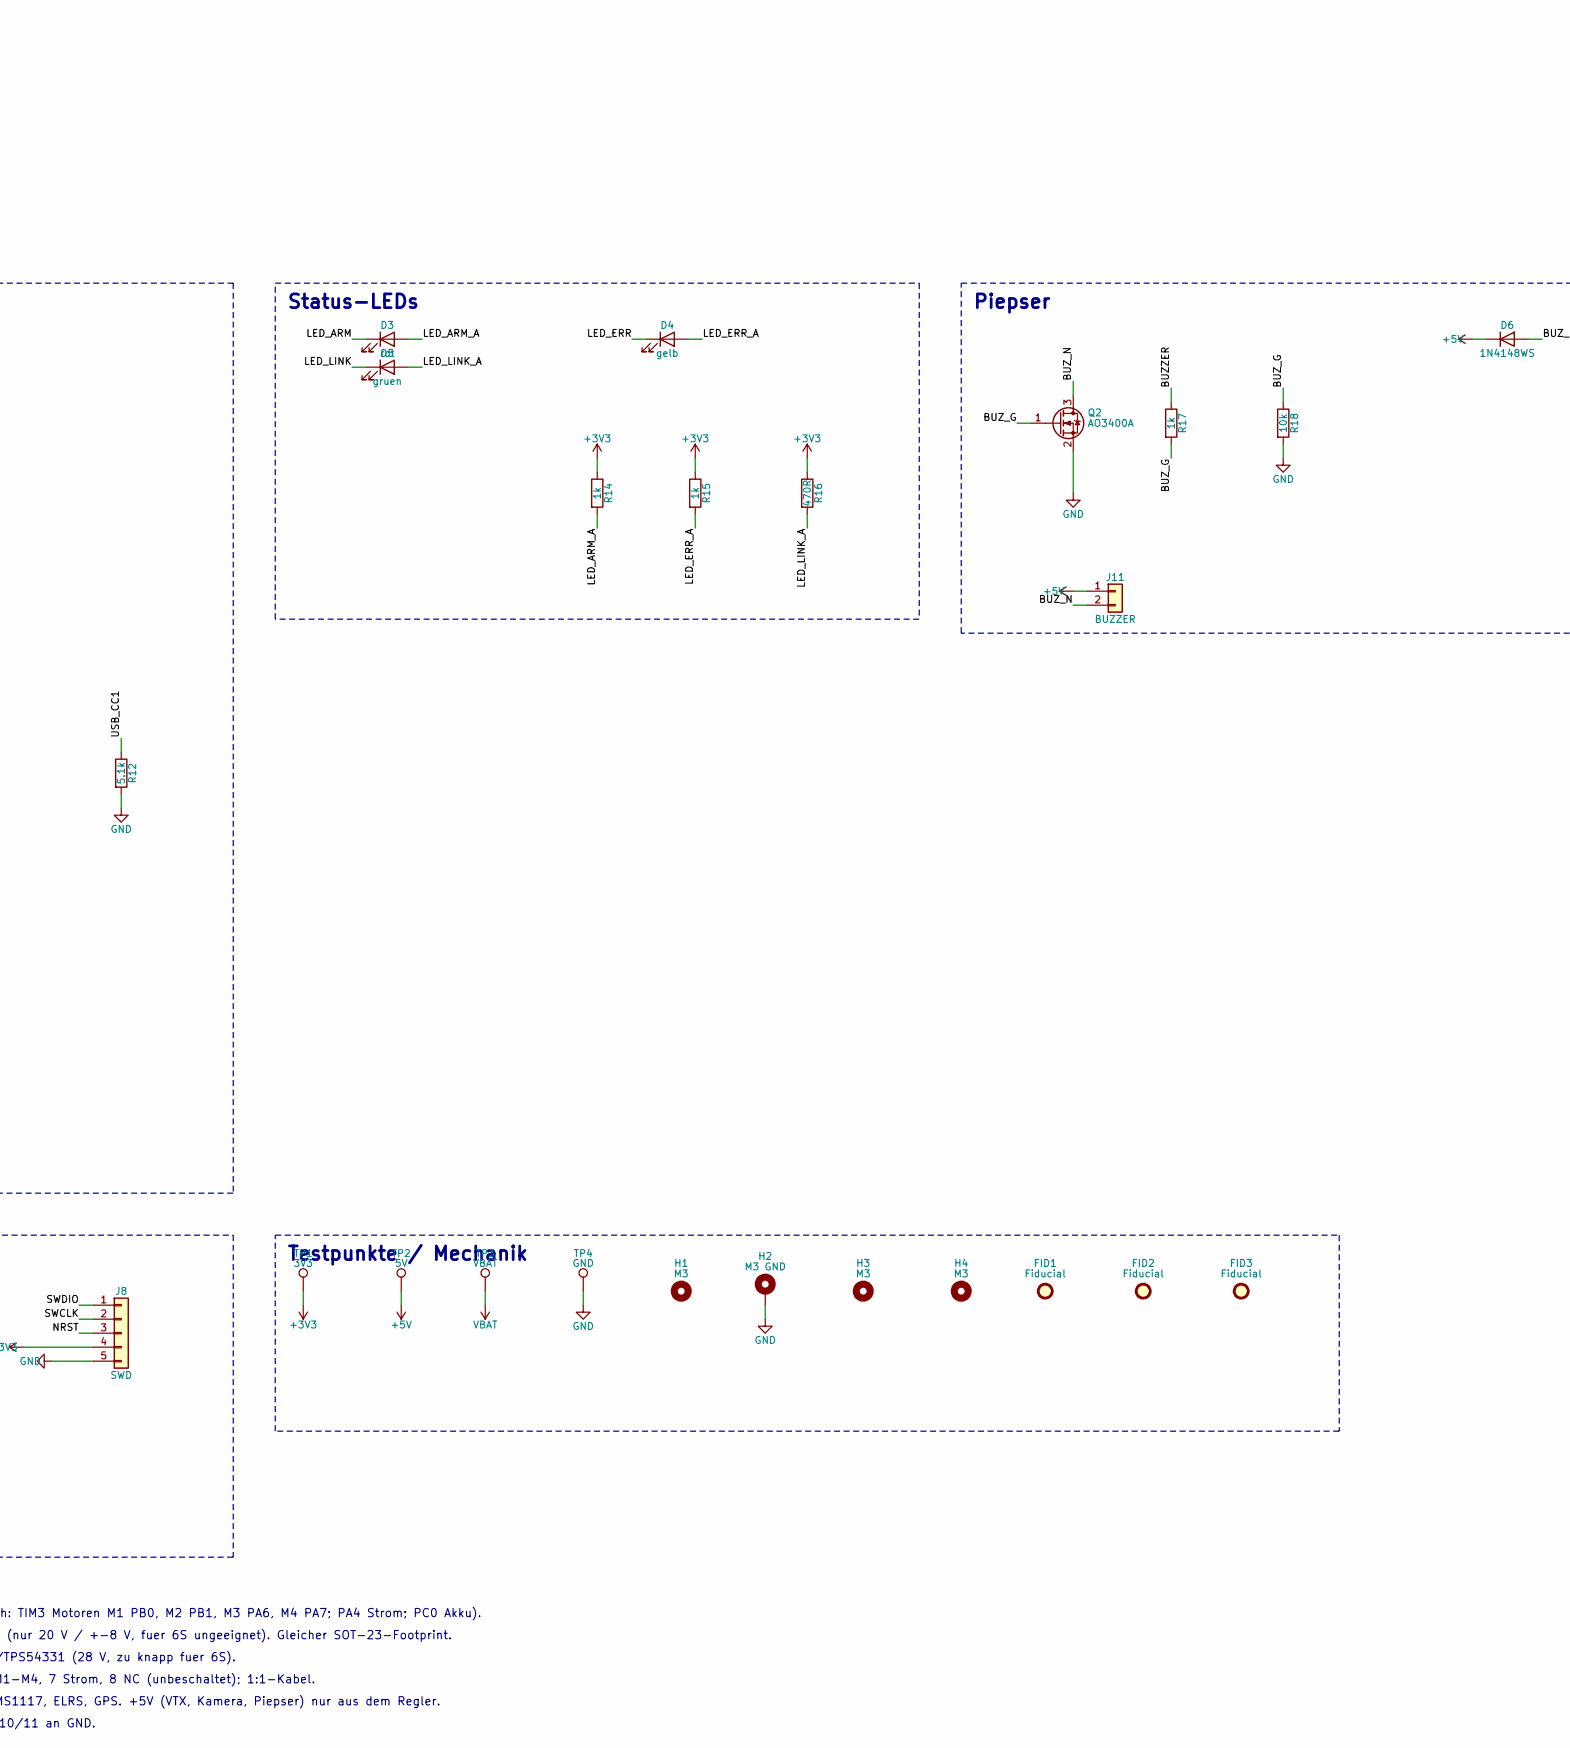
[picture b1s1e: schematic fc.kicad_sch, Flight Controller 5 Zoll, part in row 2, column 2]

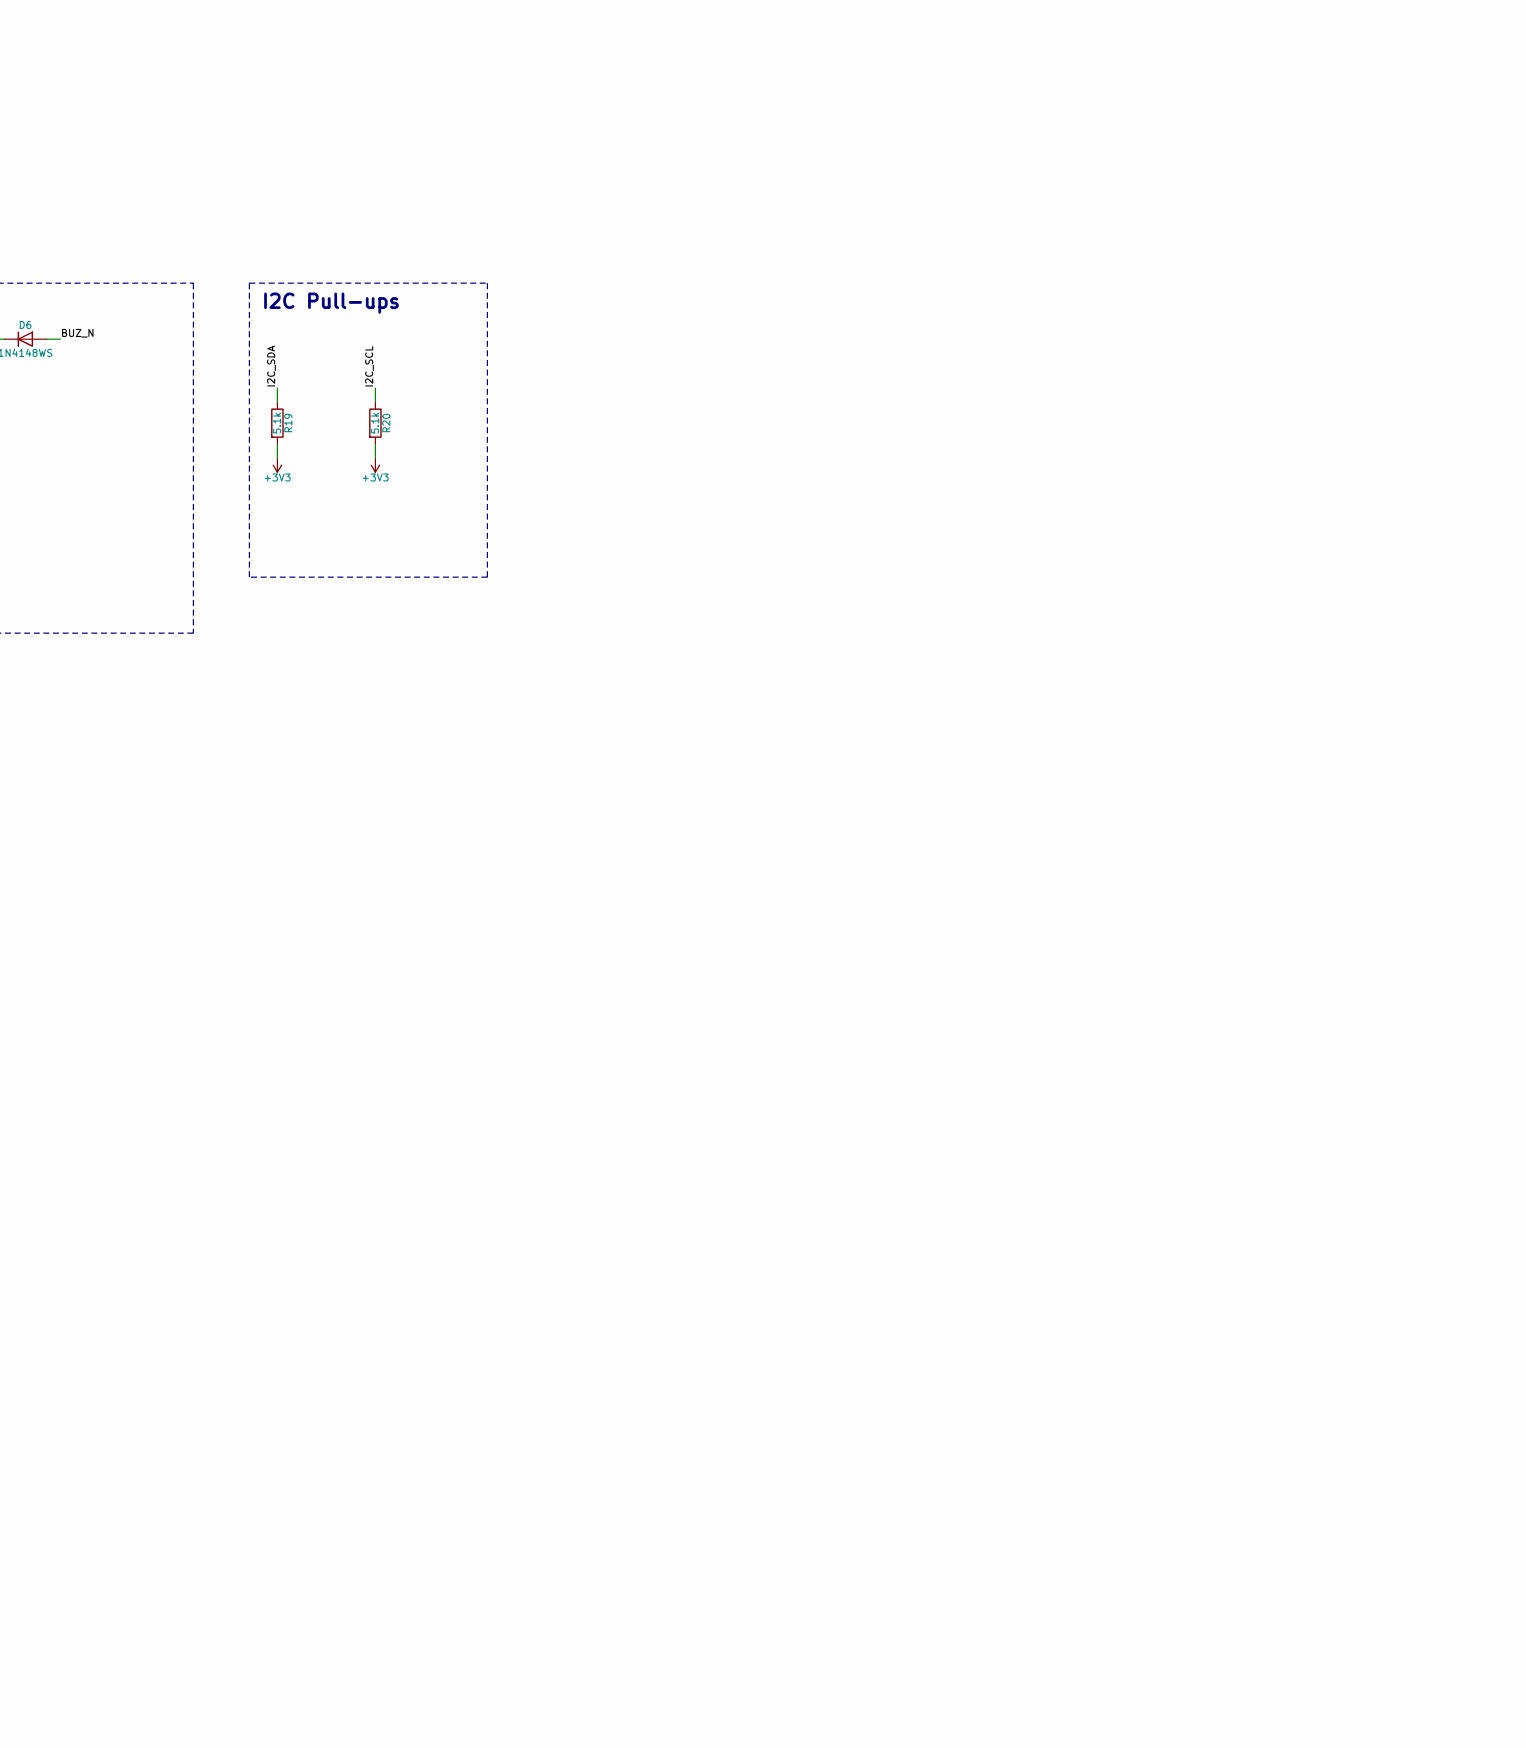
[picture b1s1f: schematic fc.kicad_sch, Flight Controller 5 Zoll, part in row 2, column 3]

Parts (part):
C1, C2, C3, C4, C5, C7, C11, C14, C15, C16, C18, C20, C24, C28, C30, C32, C34: 100nF; C_0402_1005Metric; LCSC C307331
C6, C29, C33: 10uF/25V; C_0603_1608Metric; LCSC C96446
C8, C25: 1uF; C_0402_1005Metric; LCSC C52923
C9, C10, C17: 2.2uF; C_0402_1005Metric; LCSC C12530
C12, C13: 18pF; C_0402_1005Metric; LCSC C1549
C21: 47uF/35V; CP_Elec_6.3x5.4; LCSC C48970990
C22: 10uF/50V; C_1210_3225Metric; LCSC C17498688
C23: 100nF/50V; C_0402_1005Metric; LCSC C307331
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
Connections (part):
+3V3: C1.1, C2.1, C3.1, C4.1, C5.1, C6.1, C16.1, C17.1, C18.1, C20.1, C31.1, C32.1, FB1.1, J4.3, J8.4, J9.3, J10.7, JP1.2 (B), R7.2, R8.2, R14.1, R15.1, R16.1, R19.2, R20.2, TP1.1, U1.1 (VBAT), U1.19 (VDD), U1.32 (VDD), U1.48 (VDD), U1.64 (VDD), U2.5 (VDDIO), U2.8 (VDD), U3.3 (IO2), U3.7 (IO3), U3.8 (VCC), U5.2 (VO)
+3V3A: C7.1, C8.1, FB1.2, U1.13 (VDDA)
+4V5: C29.1, C30.1, D2.1 (K), D7.1 (K), J3.3, J5.3, U5.3 (VI)
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
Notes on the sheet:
Flight Controller 5 Zoll - STM32F405 / ICM-42688-P / W25Q128
Prozessor STM32F405RGT6
Gyro ICM-42688-P (SPI1)
Blackbox-Flash W25Q128 (SPI1)
Messung Akkuspannung / Strom
Eingang 2-6S, Verpolschutz
5-V-Schaltregler
3,3-V-Regler
USB-C
Status-LEDs
Piepser
I2C Pull-ups
Steckverbinder
Testpunkte / Mechanik
Versorgungsmarkierungen (PWR_FLAG) fuer die elektrische Regelpruefung
Hinweise:
- Pinbelegung MCU siehe README.md (verbindlich: TIM3 Motoren M1 PB0, M2 PB1, M3 PA6, M4 PA7; PA4 Strom; PC0 Akku).
- Q1: Si2319CDS (40 V / +-20 V) statt SI2301 (nur 20 V / +-8 V, fuer 6S ungeeignet). Gleicher SOT-23-Footprint.
- U4: LMR33630B (36 V Eingang) statt MP1584/TPS54331 (28 V, zu knapp fuer 6S).
- J2 ESC (B-Cube 4in1): 1 GND, 2 VBAT, 3-6 M1-M4, 7 Strom, 8 NC (unbeschaltet); 1:1-Kabel.
- +4V5: USB (D2) oder 5-V-Regler (D7) -> AMS1117, ELRS, GPS. +5V (VTX, Kamera, Piepser) nur aus dem Regler.
- U2 Pin 2/3 RESV laut Referenzdesign frei, 7/10/11 an GND.
